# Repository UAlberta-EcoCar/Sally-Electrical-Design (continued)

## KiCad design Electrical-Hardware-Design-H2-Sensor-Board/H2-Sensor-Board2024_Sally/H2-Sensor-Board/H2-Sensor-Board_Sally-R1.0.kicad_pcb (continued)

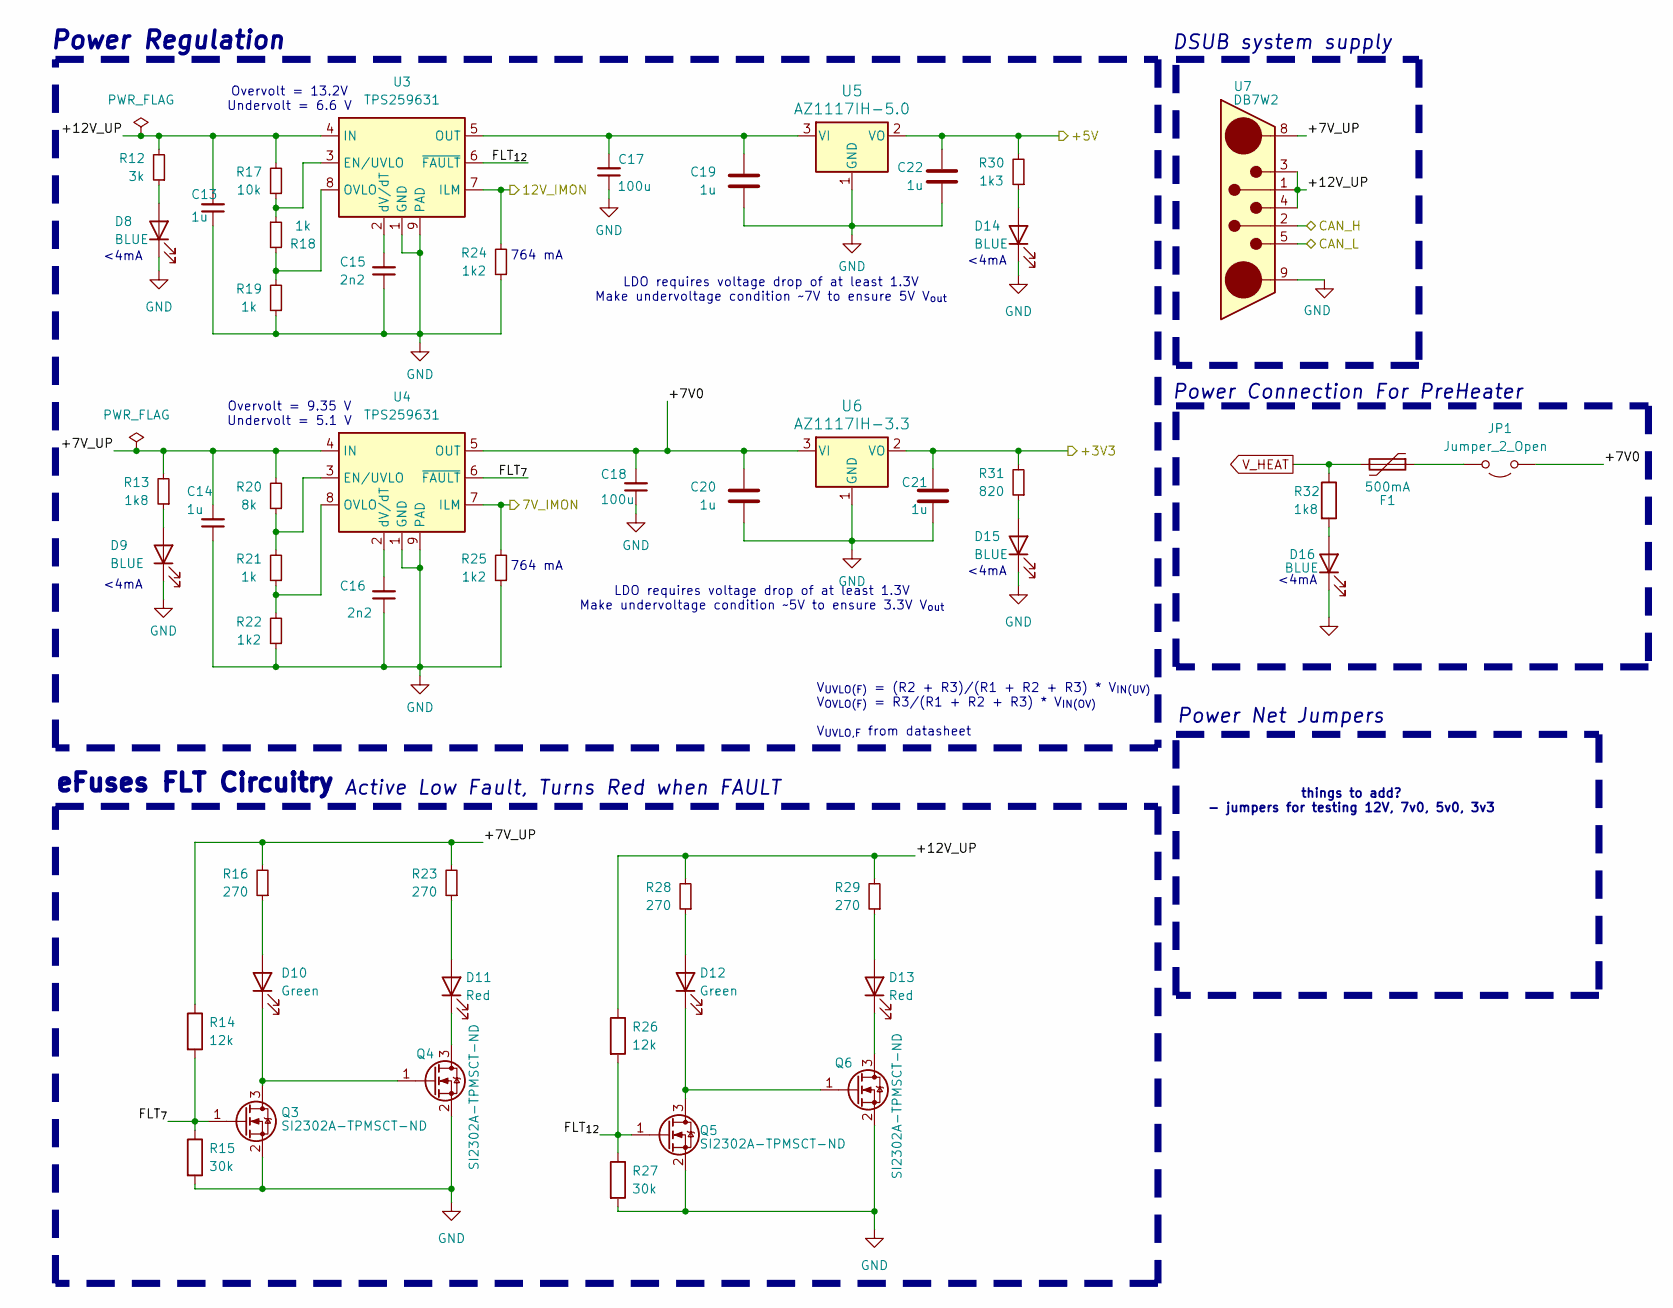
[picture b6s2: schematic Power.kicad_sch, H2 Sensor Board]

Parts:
C13, C14: 1u; C_0603_1608Metric; Part# C15849
C15, C16: 2n2; C_0603_1608Metric; Part# C1525
C17, C18: 100u; C_1210_3225Metric; Part# C7432790
C19, C20, C21, C22: 1u; C_0603_1608Metric
D8, D9, D14, D15: BLUE; LED_0603_1608Metric_Pad1.05x0.95mm_HandSolder; Part# C72041
D10, D12: Green; LED_0603_1608Metric_Pad1.05x0.95mm_HandSolder; Part# C72043
D11, D13: Red; LED_0603_1608Metric_Pad1.05x0.95mm_HandSolder; Part# C72043
D16: BLUE; LED_0603_1608Metric_Pad1.05x0.95mm_HandSolder
F1: 500mA; Fuse_0805_2012Metric
JP1: Jumper_2_Open; J_0603_Triangular
Q3, Q4, Q5, Q6: SI2302A-TPMSCT-ND; SOT-23-3_Adjusted; Part# SI2302A-TPMSCT-ND
R12: 3k; R_0603_1608Metric; Part# C23253
R13: 1k8; R_0603_1608Metric; Part# C23253
R14, R26: 12k; R_0603_1608Metric
R15, R27: 30k; R_0603_1608Metric
R16, R23, R28, R29: 270; R_0603_1608Metric; Part# C22966
R17: 10k; R_0603_1608Metric
R18, R19, R21: 1k; R_0603_1608Metric
R20: 8k; R_0603_1608Metric
R22, R24, R25: 1k2; R_0603_1608Metric
R30: 1k3; R_0603_1608Metric; Part# C23253
R31: 820; R_0603_1608Metric; Part# C23253
R32: 1k8; R_0603_1608Metric; JLCPCB Part#(Optional) C28636
U3, U4: TPS259631; TI_SO-PowerPAD-8
U5: AZ1117IH-5.0; SOT-223-3_TabPin2
U6: AZ1117IH-3.3; SOT-223-3_TabPin2
U7: DB7W2; DB7W2-Male

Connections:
+5V: C22.1, R30.2, U5.2 (VO); also elsewhere on the board
/7V_IMON: R25.2, U4.7 (ILM); also elsewhere on the board
/12V_IMON: R24.2, U3.7 (ILM); also elsewhere on the board
/CAN_H: U7.2; also elsewhere on the board
/CAN_L: U7.5; also elsewhere on the board
/Power/+7V0: C18.2, C20.1, JP1.1 (A), U4.5 (OUT), U6.3 (VI)
/Power/+7V_UP: C14.2, R13.2, R14.1, R16.2, R20.2, R23.2, U4.4 (IN), U7.8
/Power/+12V_UP: C13.2, R12.2, R17.2, R26.1, R28.2, R29.2, U3.4 (IN), U7.1, U7.3, U7.4
/Power/FLT_{7}: Q3.1 (G), R14.2, R15.1, U4.6 (~FAULT)
/Power/FLT_{12}: Q5.1 (G), R26.2, R27.1, U3.6 (~FAULT)
GND: C13.1, C14.1, C15.1, C16.1, C17.1, C18.1, C19.2, C20.2, C21.2, C22.2, D8.1 (K), D9.1 (K), D14.1 (K), D15.1 (K), D16.1 (K), Q3.2 (S), Q4.2 (S), Q5.2 (S), Q6.2 (S), R15.2, R19.1, R22.1, R24.1, R25.1, R27.2, U3.1 (GND), U3.9 (PAD), U4.1 (GND), U4.9 (PAD), U5.1 (GND), U6.1 (GND), U7.9; also elsewhere on the board
unnamed: D8.2 (A), R12.1
unnamed: D9.2 (A), R13.1
unnamed: D10.2 (A), R16.1
unnamed: D10.1 (K), Q3.3 (D), Q4.1 (G)
unnamed: D11.2 (A), R23.1
unnamed: D11.1 (K), Q4.3 (D)
unnamed: D12.2 (A), R28.1
unnamed: D12.1 (K), Q5.3 (D), Q6.1 (G)
unnamed: D13.2 (A), R29.1
unnamed: D13.1 (K), Q6.3 (D)
unnamed: D14.2 (A), R30.1
unnamed: D15.2 (A), R31.1
unnamed: D16.2 (A), R32.2
unnamed: F1.1, JP1.2 (B)
unnamed: R17.1, R18.1, U3.3 (EN/UVLO)
unnamed: C17.2, C19.1, U3.5 (OUT), U5.3 (VI)
unnamed: R18.2, R19.2, U3.8 (OVLO)
unnamed: C15.2, U3.2 (dV/dT)
unnamed: R20.1, R21.2, U4.3 (EN/UVLO)
unnamed: R21.1, R22.2, U4.8 (OVLO)
unnamed: C16.2, U4.2 (dV/dT)
V_HEAT: F1.2, R32.1; also elsewhere on the board

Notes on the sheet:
DSUB system supply
<4mA
LDO requires voltage drop of at least 1.3V Make undervoltage condition ~7V to ensure 5V V_{out}
Power Connection For PreHeater
LDO requires voltage drop of at least 1.3V Make undervoltage condition ~5V to ensure 3.3V V_{out}
V_{UVLO(F)} = (R2 + R3)/(R1 + R2 + R3) * V_{IN(UV)} V_{OVLO(F)} = R3/(R1 + R2 + R3) * V_{IN(OV)} V_{UVLO,F} from datasheet
things to add? - jumpers for testing 12V, 7v0, 5v0, 3v3
Overvolt = 9.35 V Undervolt = 5.1 V
764 mA
Active Low Fault, Turns Red when FAULT
eFuses FLT Circuitry
Power Net Jumpers
Overvolt = 13.2V Undervolt = 6.6 V
Power Regulation

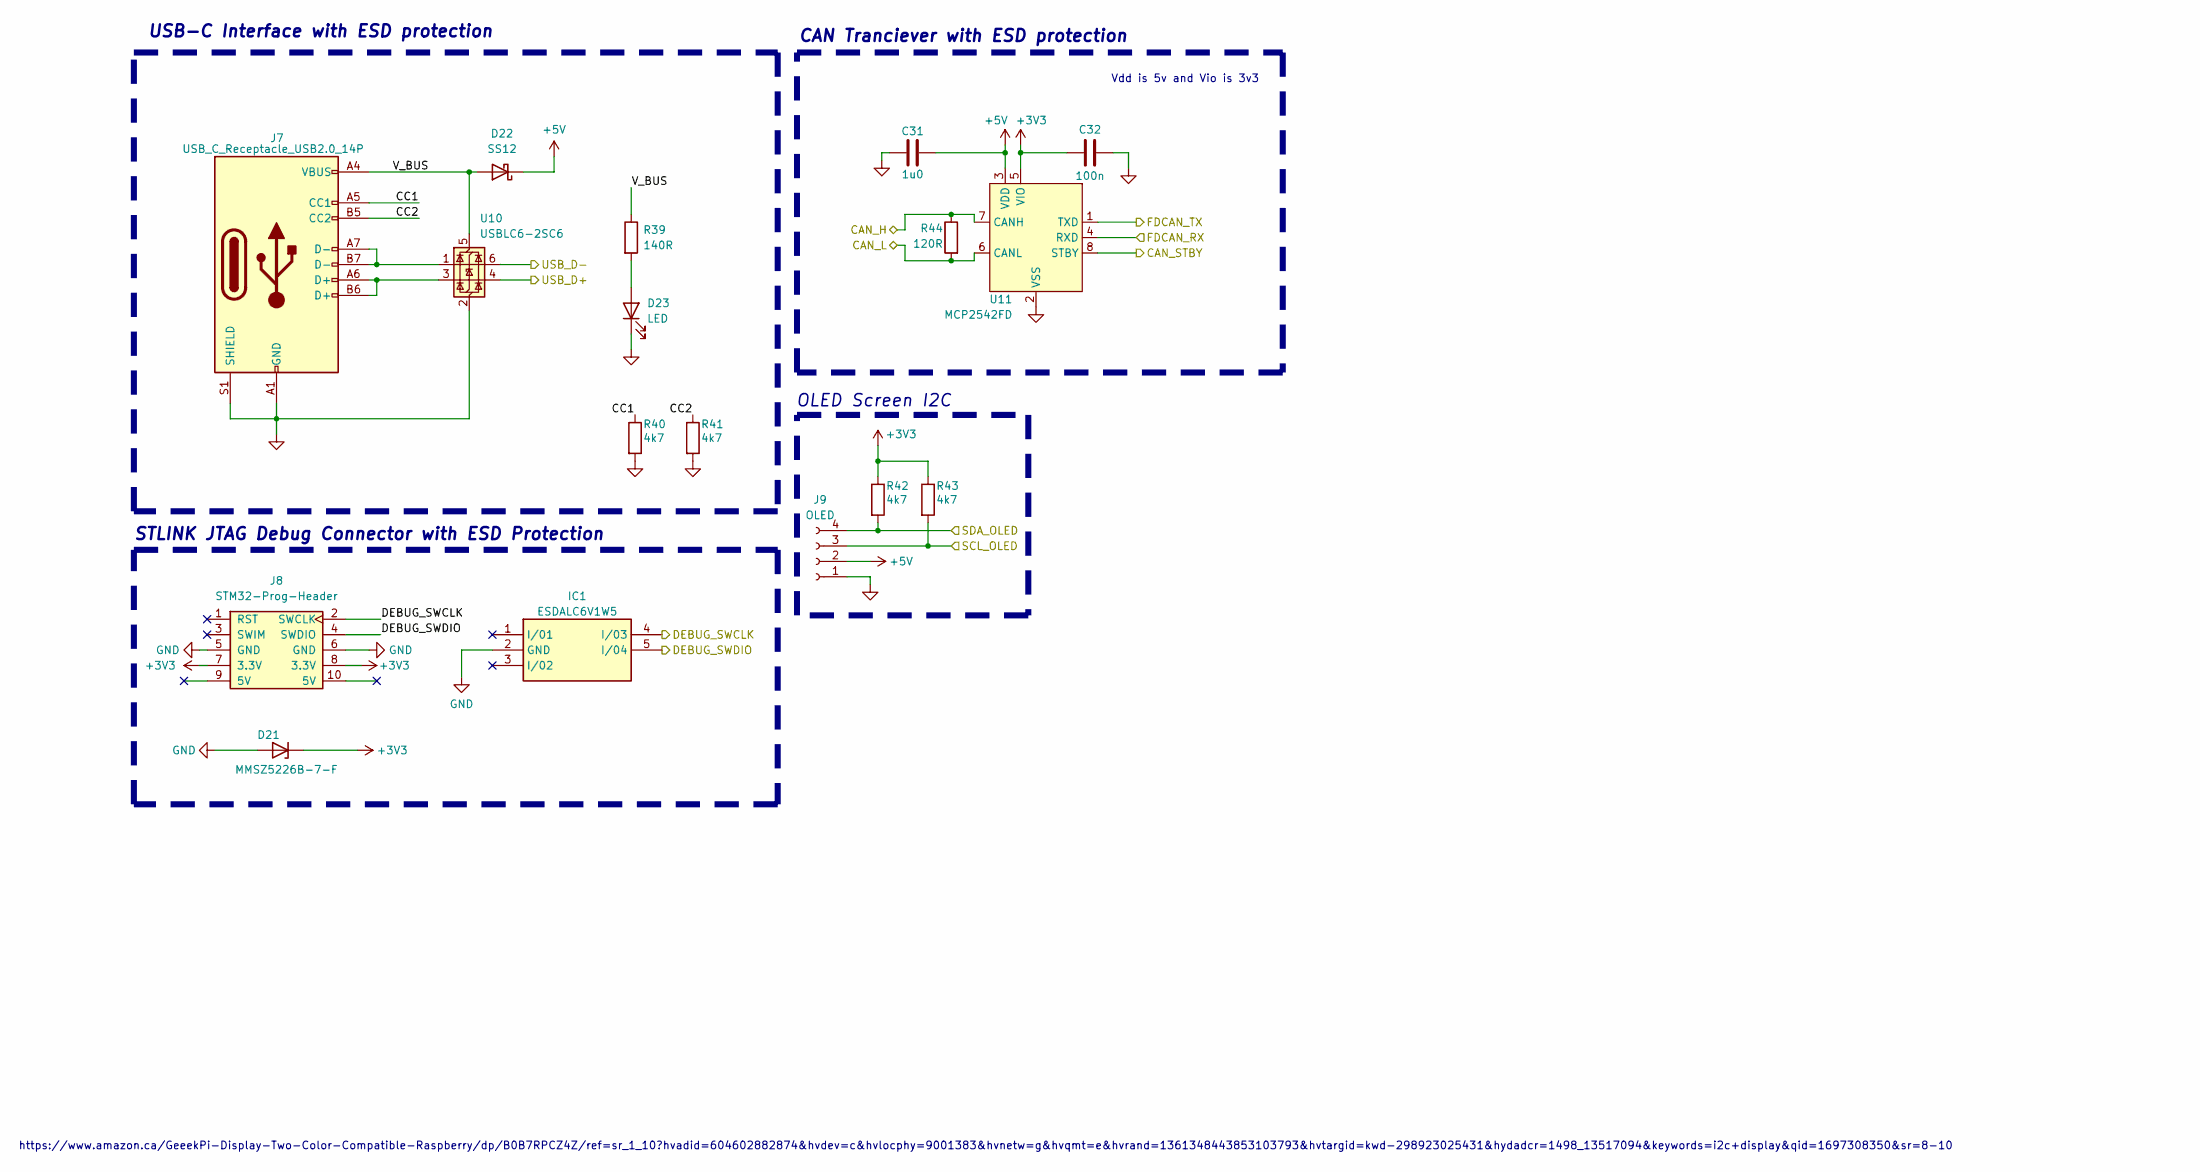
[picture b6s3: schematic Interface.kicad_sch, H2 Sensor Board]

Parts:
C31: 1u0; C_0603_1608Metric; JLCPCB Part#(Optional) C1525
C32: 100n; C_0603_1608Metric; JLCPCB Part#(Optional) C1525
D21: MMSZ5226B-7-F; D_SOD-123; Digikey # MMSZ5226B-FDICT-ND
D22: SS12; D_SMA
D23: LED; LED_0603_1608Metric_Pad1.05x0.95mm_HandSolder
IC1: ESDALC6V1W5; SOT65P210X110-5N; JLCPCB Part#(Optional) C2827626
J7: USB_C_Receptacle_USB2.0_14P; USB_C_Receptacle_GCT_USB4105-xx-A_16P_TopMnt_Horizontal
J8: STM32-Prog-Header; IDC-STM32-Prog-Header_2x05_P2.54mm_Vertical
J9: OLED; Display_128x64_096_I2C
R39: 140R; R_0603_1608Metric
R40, R41, R42, R43: 4k7; R_0603_1608Metric; JLCPCB Part#(Optional) C23162
R44: 120R; R_0603_1608Metric
U10: USBLC6-2SC6; SOT-23-6
U11: MCP2542FD; SOIC-8_3.9x4.9mm_P1.27mm

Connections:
+5V: C31.2, D22.1 (K), J9.2, U11.3 (VDD); also elsewhere on the board
/CAN_H: R44.1, U11.7 (CANH); also elsewhere on the board
/CAN_L: R44.2, U11.6 (CANL); also elsewhere on the board
/CAN_STBY: U11.8 (STBY); also elsewhere on the board
/DEBUG_SWCLK: IC1.4 (I/03), J8.2 (SWCLK); also elsewhere on the board
/DEBUG_SWDIO: IC1.5 (I/04), J8.4 (SWDIO); also elsewhere on the board
/FDCAN_RX: U11.4 (RXD); also elsewhere on the board
/FDCAN_TX: U11.1 (TXD); also elsewhere on the board
/Interface/CC1: J7.A5 (CC1), R40.1
/Interface/CC2: J7.B5 (CC2), R41.1
/Interface/V_BUS: D22.2 (A), J7.A4 (VBUS), J7.A9 (VBUS), J7.B4 (VBUS), J7.B9 (VBUS), R39.1, U10.5 (VBUS)
/SCL_OLED: J9.3, R43.2; also elsewhere on the board
/SDA_OLED: J9.4, R42.2; also elsewhere on the board
/USB_D-: U10.6 (I/O1); also elsewhere on the board
GND: C31.1, C32.1, D21.2 (A), D23.1 (K), IC1.2 (GND), J7.A1 (GND), J7.A12 (GND), J7.B1 (GND), J7.B12 (GND), J7.S1 (SHIELD), J8.5 (GND), J8.6 (GND), J9.1, R40.2, R41.2, U10.2 (GND), U11.2 (VSS); also elsewhere on the board
unnamed: D23.2 (A), R39.2

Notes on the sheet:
Vdd is 5v and Vio is 3v3
USB-C Interface with ESD protection
STLINK JTAG Debug Connector with ESD Protection
OLED Screen I2C
https://www.amazon.ca/GeeekPi-Display-Two-Color-Compatible-Raspberry/dp/B0B7RPCZ4Z/ref=sr_1_10?hvadid=604602882874&hvdev=c&hvlocphy=9001383&hvnetw=g&hvqmt=e&hvrand=1361348443853103793&hvtargid=kwd-298923025431&hydadcr=1498_13517094&keywords=i2c+display&qid=1697308350&sr=8-10
CAN Tranciever with ESD protection

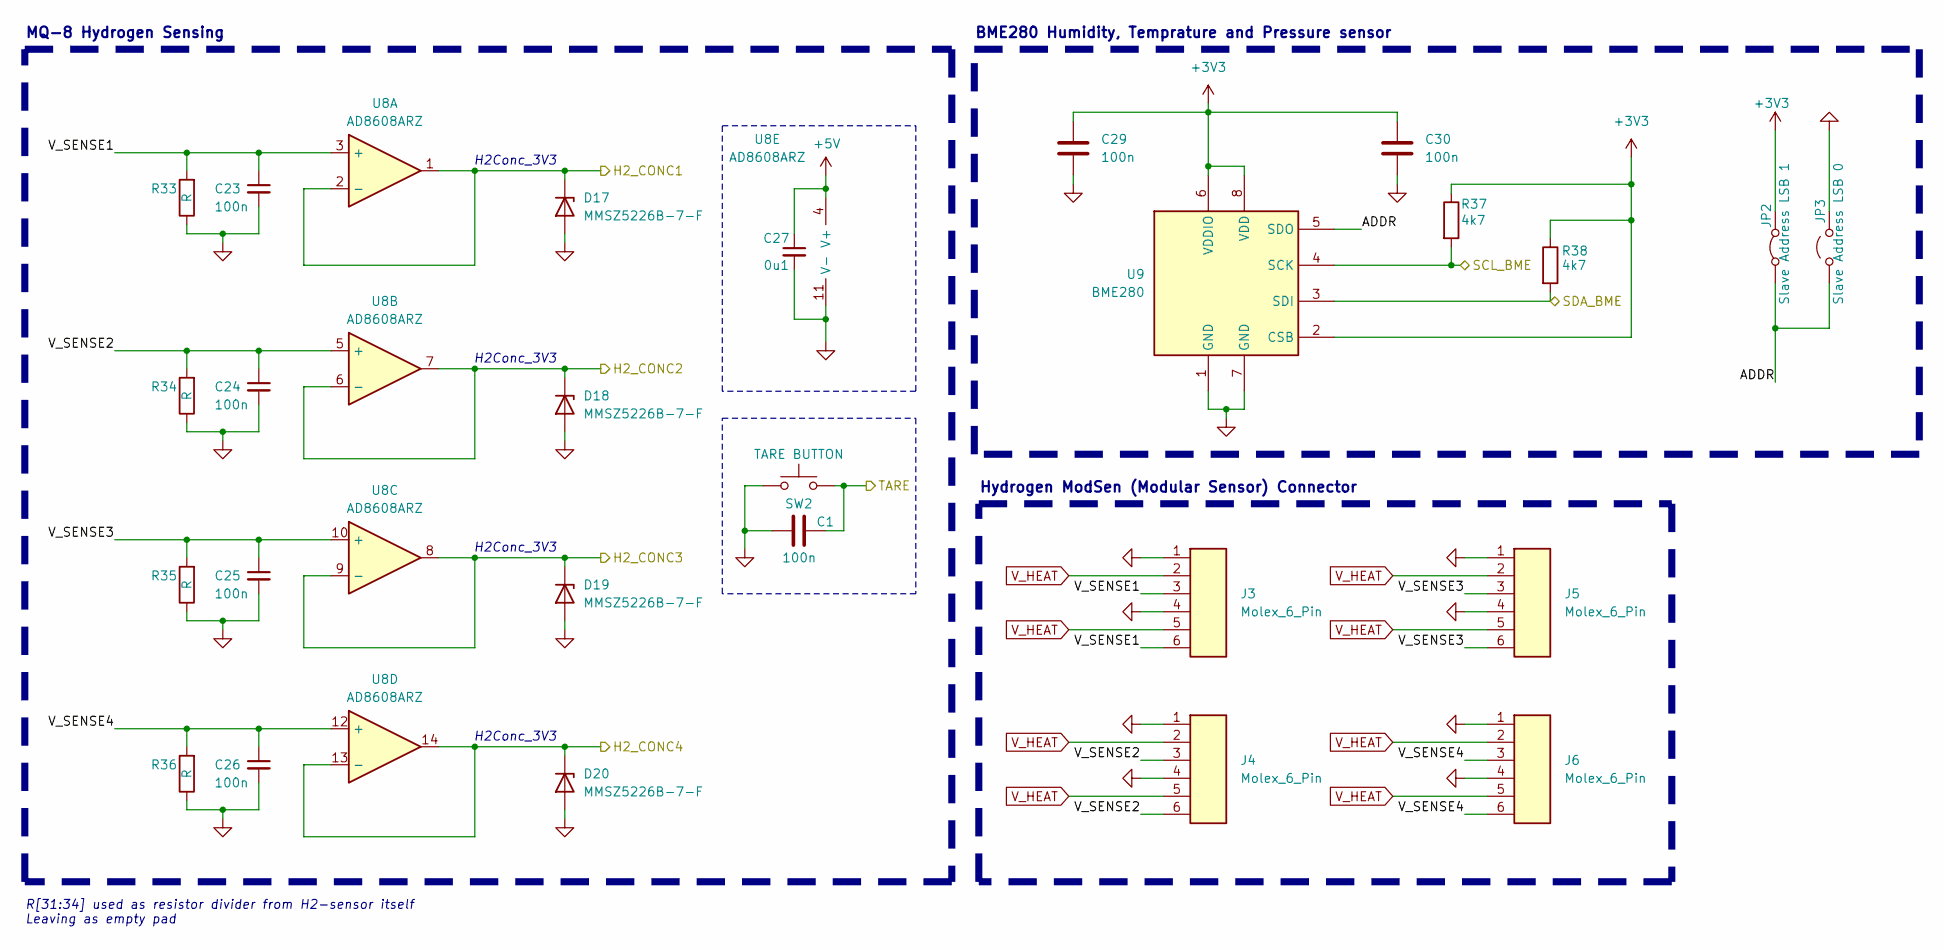
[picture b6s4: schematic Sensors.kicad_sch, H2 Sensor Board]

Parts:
C1, C29, C30: 100n; C_0603_1608Metric; JLCPCB Part#(Optional) C1525
C23, C24, C25, C26: 100n; C_0603_1608Metric; JLCPCB Part#(Optional) C14663
C27: 0u1; C_0603_1608Metric
D17, D18, D19, D20: MMSZ5226B-7-F; D_SOD-123
J3, J4, J5, J6: Molex_6_Pin; Molex_6_Pin_FTP
JP2: Slave Address LSB 1; SolderJumper-2_P1.3mm_Bridged_RoundedPad1.0x1.5mm
JP3: Slave Address LSB 0; SolderJumper-2_P1.3mm_Open_RoundedPad1.0x1.5mm
R33, R34, R35, R36: R; R_0603_1608Metric; JLCPCB Part#(Optional) C23162
R37, R38: 4k7; R_0603_1608Metric; JLCPCB Part#(Optional) C23162
SW2: TARE BUTTON; SW_PUSH_6mm_H5mm
U8: AD8608ARZ; SOIC-14_3.9x8.7mm_P1.27mm
U9: BME280; Bosch_LGA-8_2.5x2.5mm_P0.65mm_ClockwisePinNumbering

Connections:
+5V: C27.1, U8.4 (V+); also elsewhere on the board
/H2_COMP1: D17.1 (K), U8.1, U8.2 (-); also elsewhere on the board
/H2_COMP2: D18.1 (K), U8.6 (-), U8.7; also elsewhere on the board
/H2_COMP3: D19.1 (K), U8.8, U8.9 (-); also elsewhere on the board
/H2_COMP4: D20.1 (K), U8.13 (-), U8.14; also elsewhere on the board
/SCL_BME: R37.2, U9.4 (SCK); also elsewhere on the board
/SDA_BME: R38.2, U9.3 (SDI); also elsewhere on the board
/Sensors/ADDR: JP2.1 (A), JP3.1 (A), U9.5 (SDO)
/Sensors/V_SENSE1: C23.1, J3.3, J3.6, R33.2, U8.3 (+)
/Sensors/V_SENSE2: C24.1, J4.3, J4.6, R34.2, U8.5 (+)
/Sensors/V_SENSE3: C25.1, J5.3, J5.6, R35.2, U8.10 (+)
/Sensors/V_SENSE4: C26.1, J6.3, J6.6, R36.2, U8.12 (+)
GND: C1.1, C23.2, C24.2, C25.2, C26.2, C27.2, C29.2, C30.2, D17.2 (A), D18.2 (A), D19.2 (A), D20.2 (A), J3.1, J3.4, J4.1, J4.4, J5.1, J5.4, J6.1, J6.4, JP3.2 (B), R33.1, R34.1, R35.1, R36.1, SW2.1, U8.11 (V-), U9.1 (GND), U9.7 (GND); also elsewhere on the board
V_HEAT: J3.2, J3.5, J4.2, J4.5, J5.2, J5.5, J6.2, J6.5; also elsewhere on the board

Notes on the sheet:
H2Conc_3V3
BME280 Humidity, Temprature and Pressure sensor
MQ-8 Hydrogen Sensing
R[31:34] used as resistor divider from H2-sensor itself Leaving as empty pad
Hydrogen ModSen (Modular Sensor) Connector

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
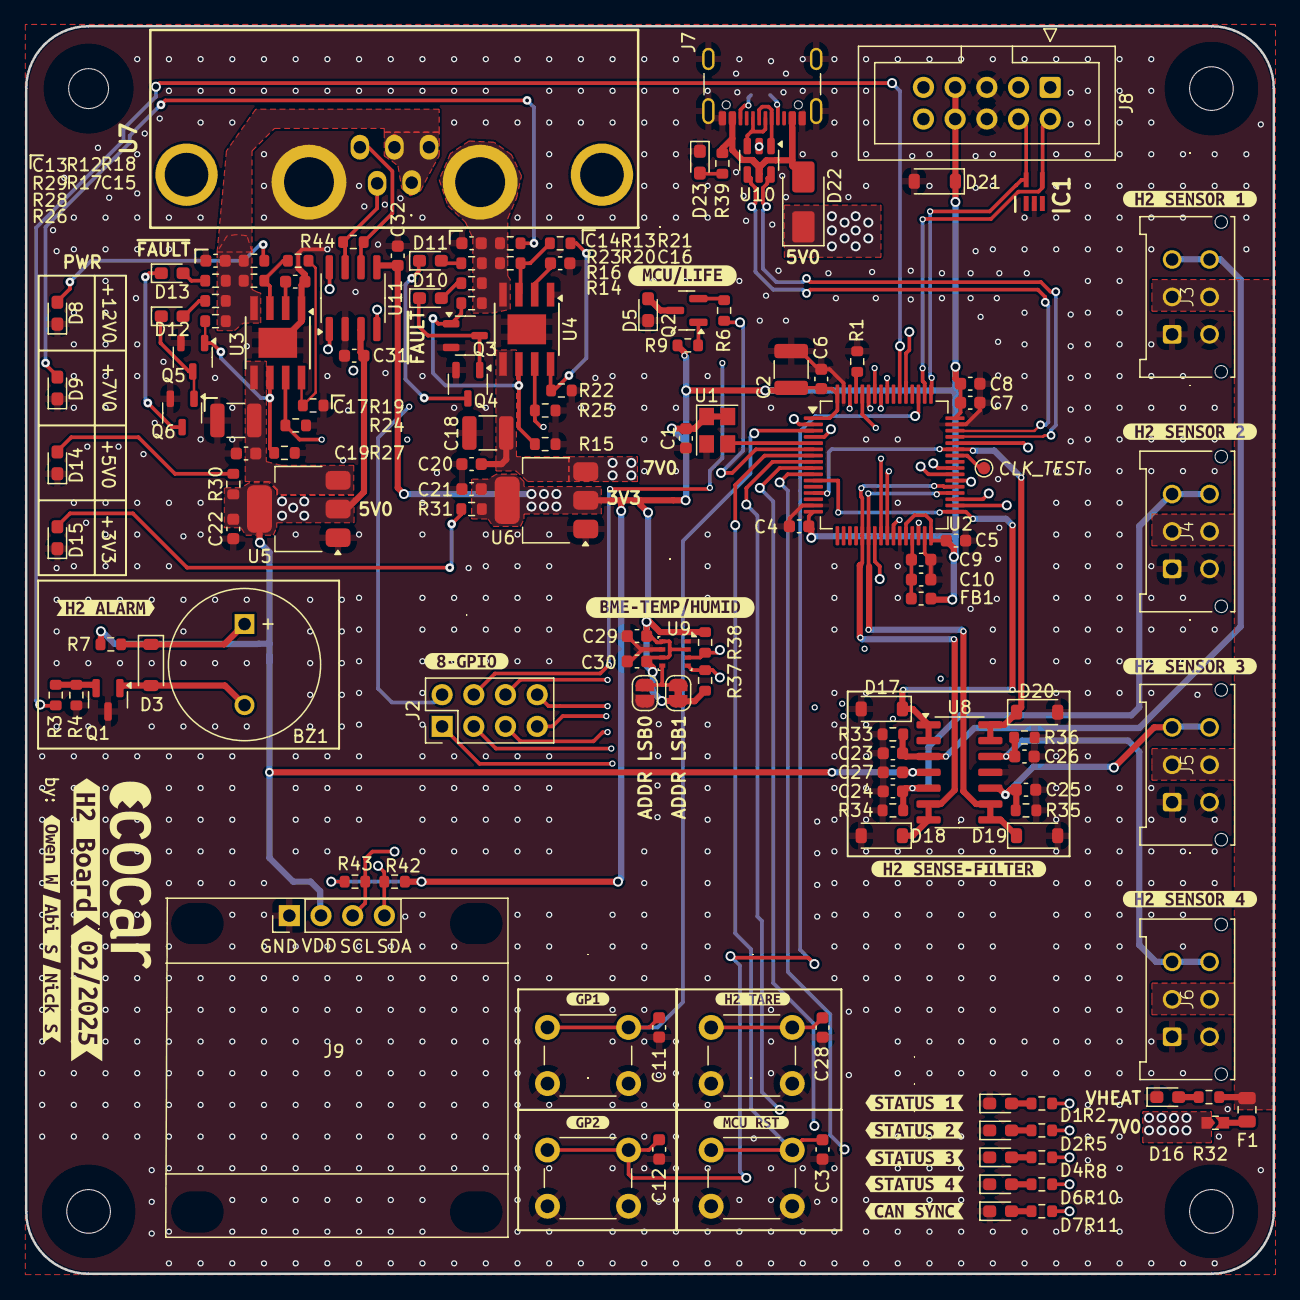
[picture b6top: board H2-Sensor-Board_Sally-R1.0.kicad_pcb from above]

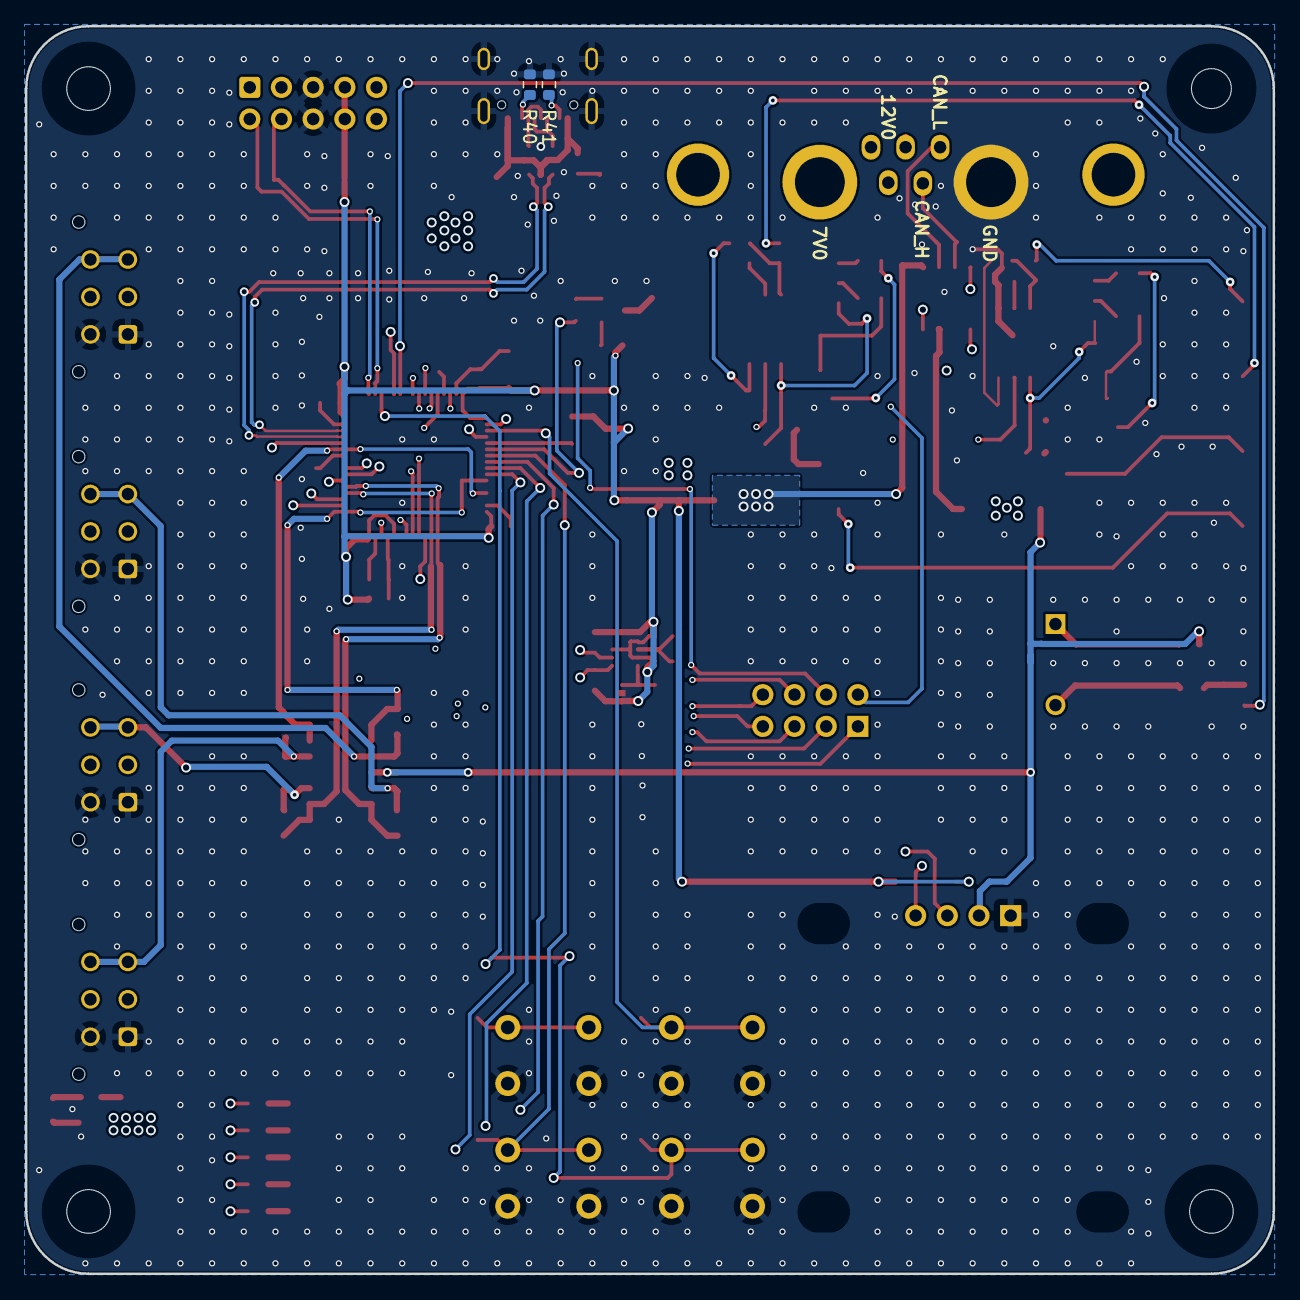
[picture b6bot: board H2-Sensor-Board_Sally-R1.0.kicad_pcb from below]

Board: 4 copper layers, 100.0 x 100.0 mm, 163 parts (2 on the bottom side), 94 nets.

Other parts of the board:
C3, C28: 100n; C_0603_1608Metric
SW1: RESET; SW_PUSH_6mm_H5mm
SW4: TARE BUTTON; SW_PUSH_6mm_H5mm
U1: 8MHz; Crystal_SMD_3225-4Pin_3.2x2.5mm
kibuzzard-67B3D4BC: G***; kibuzzard-67B3D4BC
kibuzzard-67B3D4E2: G***; kibuzzard-67B3D4E2
kibuzzard-67B3D4F1: G***; kibuzzard-67B3D4F1
kibuzzard-67B3D482: G***; kibuzzard-67B3D482
kibuzzard-67B3D604: G***; kibuzzard-67B3D604
kibuzzard-67B3F7B9: G***; kibuzzard-67B3F7B9
kibuzzard-67B7BA3C: G***; kibuzzard-67B7BA3C
kibuzzard-67B7BA4C: G***; kibuzzard-67B7BA4C
kibuzzard-67B7BA7E: G***; kibuzzard-67B7BA7E
kibuzzard-67B7BA41: G***; kibuzzard-67B7BA41
kibuzzard-67B7BA45: G***; kibuzzard-67B7BA45
kibuzzard-67B7BBB3: G***; kibuzzard-67B7BBB3
kibuzzard-67B7BBBE: G***; kibuzzard-67B7BBBE
kibuzzard-67B7BBCB: G***; kibuzzard-67B7BBCB
kibuzzard-67B7C199: G***; kibuzzard-67B7C199
kibuzzard-67B8F9C4: G***; kibuzzard-67B8F9C4
kibuzzard-67B8F9E7: G***; kibuzzard-67B8F9E7
kibuzzard-67B41E4C: G***; kibuzzard-67B41E4C
kibuzzard-67B41E31: G***; kibuzzard-67B41E31
kibuzzard-67B41E42: G***; kibuzzard-67B41E42
kibuzzard-67B41E69: G***; kibuzzard-67B41E69
kibuzzard-67B42CCA: G***; kibuzzard-67B42CCA
kibuzzard-67B42781: G***; kibuzzard-67B42781

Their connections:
/H2_TARE: C28.2, SW4.2; also elsewhere on the board
GND: C3.1, C28.1, SW1.1, SW4.1, U1.2 (GND); also elsewhere on the board

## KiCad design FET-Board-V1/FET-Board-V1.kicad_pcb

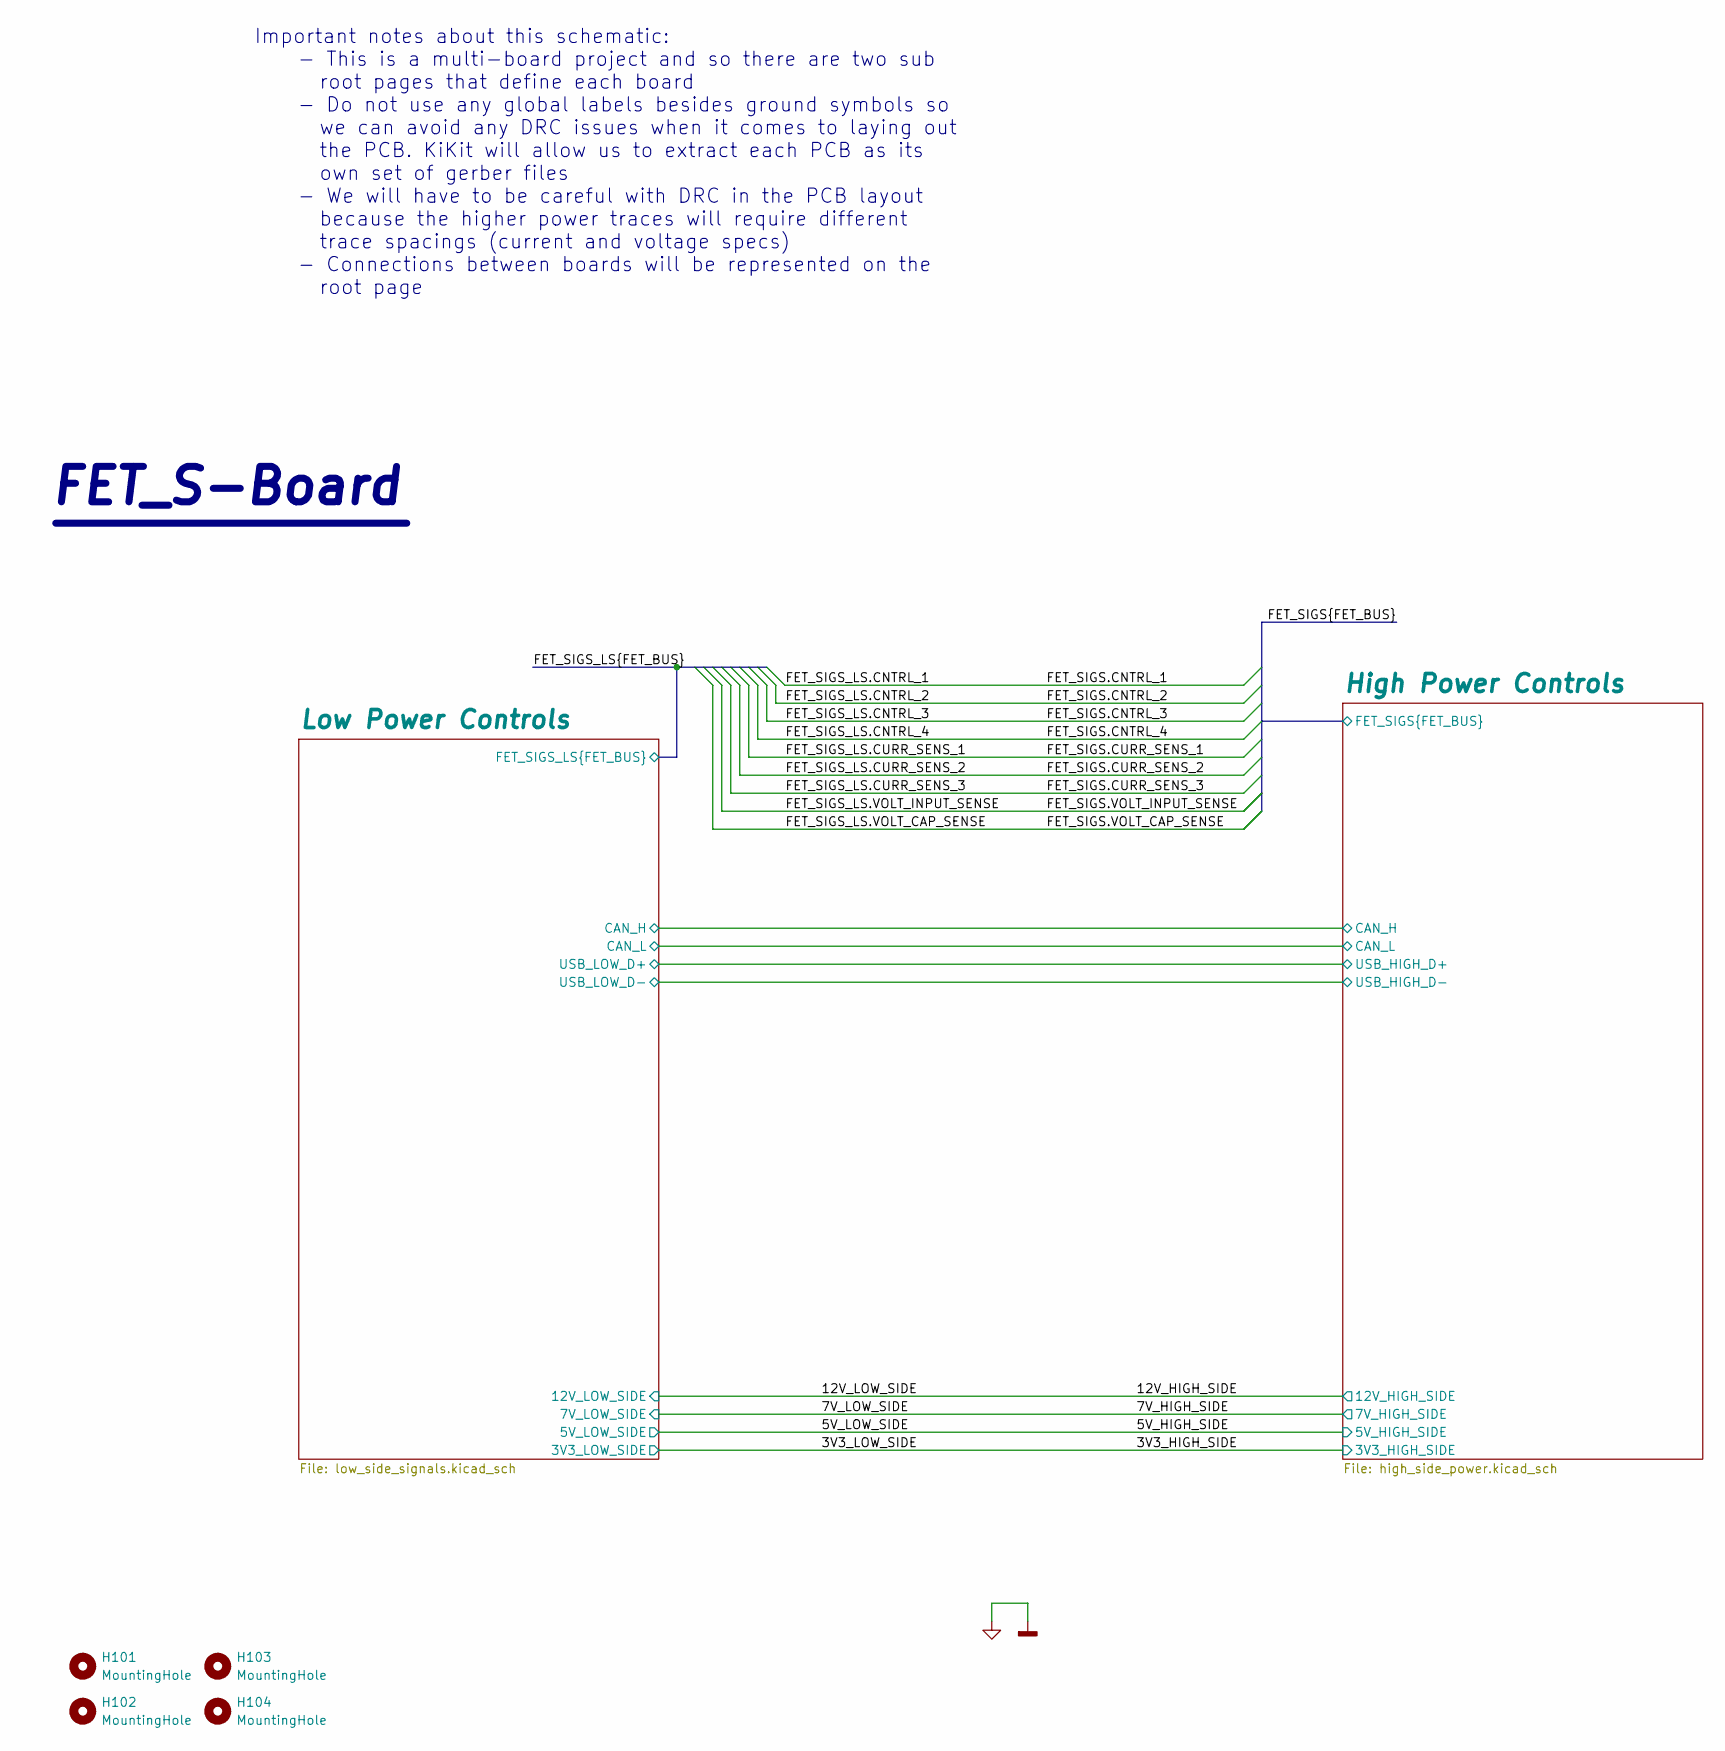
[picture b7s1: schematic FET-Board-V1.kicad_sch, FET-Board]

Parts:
H101, H102, H103, H104: MountingHole; MountingHole_3.5mm

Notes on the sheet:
FET_S-Board
Important notes about this schematic: - This is a multi-board project and so there are two sub root pages that define each board - Do not use any global labels besides ground symbols so we can avoid any DRC issues when it comes to laying out the PCB. KiKit will allow us to extract each PCB as its o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

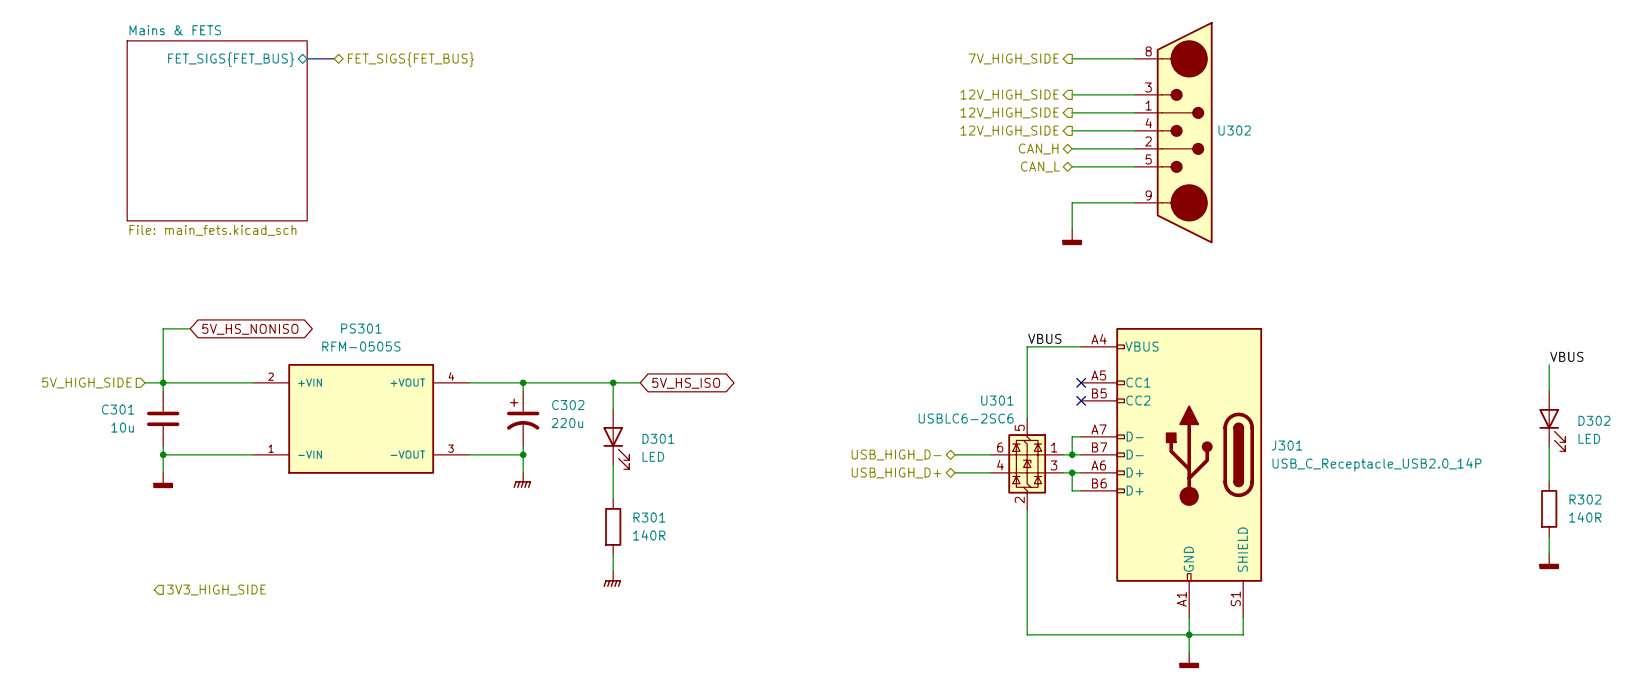
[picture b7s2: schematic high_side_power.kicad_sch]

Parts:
C301: 10u; C_0603_1608Metric
C302: 220u; CP_Elec_3x5.3
D301, D302: LED; LED_0603_1608Metric
J301: USB_C_Receptacle_USB2.0_14P; USB_C_Receptacle_GCT_USB4105-xx-A_16P_TopMnt_Horizontal
PS301: RFM-0505S; CONV_RFM-0505S; PARTREV 0
R301, R302: 140R; R_0603_1608Metric
U301: USBLC6-2SC6; SOT-23-6
U302: DB7W2-Male

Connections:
5V_HS_ISO: C302.1, D301.2 (A), PS301.4 (+VOUT); also elsewhere on the board
5V_HS_NONISO: C301.1, PS301.2 (+VIN); also elsewhere on the board
/7V_HIGH_SIDE: U302.8; also elsewhere on the board
/12V_HIGH_SIDE: U302.1, U302.3, U302.4; also elsewhere on the board
/High Power Controls/CAN_H: U302.2; also elsewhere on the board
/High Power Controls/CAN_L: U302.5; also elsewhere on the board
/High Power Controls/USB_HIGH_D+: U301.4 (I/O2); also elsewhere on the board
/High Power Controls/USB_HIGH_D-: U301.6 (I/O1); also elsewhere on the board
/High Power Controls/VBUS: D302.2 (A), J301.A4 (VBUS), J301.A9 (VBUS), J301.B4 (VBUS), J301.B9 (VBUS), U301.5 (VBUS)
GNDPWR: C302.2, PS301.3 (-VOUT), R301.2; also elsewhere on the board
unnamed: D301.1 (K), R301.1
unnamed: D302.1 (K), R302.1
unnamed: J301.A6 (D+), J301.B6 (D+), U301.3 (I/O2)
unnamed: J301.A7 (D-), J301.B7 (D-), U301.1 (I/O1)
